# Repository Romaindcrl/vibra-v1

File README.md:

# Vibra V1

Détecteur de vibrations **XIAO ESP32S3 + LIS3DH**. Carte de **48 × 38 mm**, 2 couches, prévue pour être soudée à la main. **Révision E-HS.**

## Les fichiers utiles

| Pour… | Fichier |
|---|---|
| Ouvrir ou modifier le projet | [kicad/Vibra_V1.kicad_pro](kicad/Vibra_V1.kicad_pro) — KiCad 10.0.6 ou ultérieur |
| Lire le circuit | [Schéma PDF](rendu/schema.pdf) |
| Souder et vérifier l'implantation | [Plan de montage](rendu/montage.pdf) — page 1 agrandie, page 2 à taille réelle |
| Préparer les composants | [Liste des composants](rendu/composants.csv) |
| Faire fabriquer le PCB | [Gerbers et perçages](rendu/fabrication.zip) |

Télécharger **Code → Download ZIP**, extraire le dossier, puis ouvrir le projet. Garder le dossier `kicad/` entier : les empreintes sont intégrées au PCB, et les symboles et modèles 3D sont fournis. Toutes les instructions de montage sont ci-dessous.

**Avant fabrication : confirmer que le LIS3DH acheté est l'ancien Adafruit 2809 à une seule rangée de 8 broches. La version STEMMA QT est incompatible.** L'essai mécanique à blanc et la validation du premier prototype restent à faire. Aucun firmware de détection validé n'est fourni.

L'USB-C du XIAO alimente et programme la carte. La porteuse utilise le **3,3 V** ; le **5 V reste dans le XIAO**. Pistes de puissance et liaisons thermiques GND : **0,6 mm**. Cinq LED rouges, bouton CAL, UART sans alimentation, composants 0805 à grandes pastilles.

## Montage et mise en service

<details>
<summary><strong>Ouvrir le guide de montage</strong></summary>

### Avant de faire fabriquer

1. Vérifier le module LIS3DH : **ancien Adafruit 2809, carte carrée 20,32 mm, une seule rangée de 8 broches** dans cet ordre : VIN, 3Vo, GND, SCL, SDA, SDO, CS, INT. Le modèle STEMMA QT récent n'est pas compatible, même s'il porte aussi la référence commerciale 2809. Le capteur LIS3DH est déjà soudé sur ce module.
2. Vérifier que le XIAO est bien un ESP32S3 standard, avec deux rangées de 7 broches. Imprimer la **page 2 de [montage.pdf](rendu/montage.pdf)** à **100 %, taille réelle, sans ajustement**. Mesurer le contour : 48 × 38 mm. Faire un essai à blanc avec les modules, les barrettes et le câble USB. La page 1 agrandie ×4 est réservée à la lecture, pas à cet essai.
3. Prévoir les fixations du breakout. Il doit être rigidement lié à Vibra pour mesurer ses vibrations. H5/H6 sont deux trous de 2,5 mm, entraxe 15,24 mm. Employer de la visserie M2 et deux entretoises isolantes, diamètre extérieur ≤4 mm. Hauteur cible sous le breakout : **11,04 mm au-dessus de Vibra**, pour les barrettes choisies. Une entretoise de 11 mm peut convenir après contrôle et ajustement par rondelles fines ; ne pas plier le module en serrant. Pour deux entretoises tubulaires, prévoir deux vis M2 d'environ 16 mm, deux écrous et des rondelles isolantes ; vérifier la longueur réelle et l'absence de contact avec les composants. Ces éléments génériques figurent ici, pas sous un MPN arbitraire dans la BOM électronique.

### Pièces

La [liste unique des composants](rendu/composants.csv) donne les quantités, références fabricant et repères du plan. Les barrettes mâles ne sont nécessaires que si les modules n'en ont pas déjà. TP et H désignent des pastilles de test et des trous du PCB, sans composant à acheter.

Ajouter : le PCB, un câble USB-C **de données**, l'antenne fournie avec le XIAO branchée sur son U.FL, les fixations M2 ci-dessus et, pour fixer Vibra au support mesuré, quatre fixations M3 adaptées à ce support. Pas de batterie prévue par ce dossier. Pas de port USB-C, AZ1117, PTC ni antenne à souder sur Vibra.

### Alimentation et largeur des pistes

L'USB apporte le 5 V **au XIAO**. Son régulateur fournit le 3,3 V à Vibra par U1.12. U1.14 (5V/VBUS) reste volontairement non connecté : **aucune piste 5 V ne circule sur la carte porteuse**. Ne pas relier cette broche au 3,3 V. Ne pas alimenter la carte par J2 ou un point de test.

Toutes les pistes de puissance présentes, 3V3 et GND, sont à **0,60 mm**. La masse utilise aussi des plans sur les deux faces, avec liaisons thermiques de **0,60 mm** aux pastilles et largeur minimale de cuivre de **0,60 mm**. Une règle KiCad impose cette largeur minimale aux pistes GND/3V3 et réserve la même limite aux éventuels réseaux 5V/VBUS. Les traits verts du schéma représentent des connexions logiques ; leur épaisseur sur papier n'est pas la largeur du cuivre.

Si le professeur exige une piste 5 V physiquement présente sur la porteuse, cela constitue une autre architecture à valider : la présente version respecte le choix d'alimenter uniquement par le XIAO.

### Ordre de soudure

La **page 1 de [montage.pdf](rendu/montage.pdf)** indique tous les repères, avec l'USB vers le haut. Tout se pose sur la face supérieure ; les barrettes traversantes se soudent au dos. Ne jamais souder avec l'USB branché.

1. Trier les résistances et condensateurs, puis souder R4/R7/R8/R9–R13 et C5/C6/C8/C9/C10. Ils ne sont pas polarisés. Déposer un peu d'étain sur une pastille, positionner la pièce à la pince, la fixer puis souder l'autre côté avec du flux. Les pastilles 0805 dépassent du corps pour laisser passer la panne.
2. Souder D1–D5. **Cathode K = pastille 1 = GND, à gauche sur ce plan ; anode A = pastille 2, à droite.** Vérifier la polarité du composant au mode diode avant de le poser ; ne pas se fier uniquement à sa couleur. Les cinq LED ont le même sens.
3. Souder SW2/CAL : aligner les quatre pattes avec les quatre pastilles. Le composant relie déjà 1 à 2 et 3 à 4 en interne ; l'appui relie les deux paires. Ne pas le tourner de 90°. L'orientation à 180° conserve la fonction.
4. Souder J2 et les supports femelles U1/J3. Immobiliser les barrettes perpendiculaires à la carte ; souder d'abord une broche, vérifier l'alignement, puis les autres. Garder les modules débranchés pendant la chauffe ; un gabarit mécanique hors tension peut servir à aligner les deux supports U1.
5. Si nécessaire, souder les mâles sous les modules, extrémités courtes dans les cartes et longues vers les supports. Vérifier les joints, les ponts d'étain et nettoyer les résidus selon le flux utilisé.
6. Effectuer les contrôles hors tension ci-dessous. Enficher ensuite le XIAO, **USB vers l'extérieur du bord supérieur**. Enficher le LIS3DH composants vers le haut, **VIN dans J3.1, carré, côté bas marqué 1 VIN**. Aucune broche ne doit dépasser latéralement du support. Les 0805 sous le breakout doivent avoir été soudés avant cette étape.
7. Fixer le breakout à H5/H6 sans fléchir son PCB. Fixer Vibra au support à mesurer par ses quatre trous M3. Prévoir l'emplacement de l'antenne XIAO dans le boîtier, à l'écart du métal ; elle et les entretoises ne sont pas représentées en 3D.

La masse à 0,6 mm absorbe davantage de chaleur qu'une piste signal : chauffer ensemble la patte et la pastille, utiliser du flux et une panne adaptée. Les liaisons thermiques sont conservées pour faciliter cette opération ; ne pas compenser un mauvais contact par une chauffe prolongée du composant.

### Contrôles avant le premier branchement

Modules retirés et USB débranché : vérifier l'absence de pont entre 3V3 (TP3) et GND (TP4). Un bref bip dû à la charge des condensateurs n'est pas à lui seul un court-circuit ; une résistance très faible persistante exige de rechercher le défaut. Ne pas mesurer la résistance sur une carte alimentée.

Vérifier au multimètre : TP4 ↔ U1.13/J2.1/J3.3/J3.6 ; TP3 ↔ U1.12/J3.1/J3.7 ; CAL TP6 ↔ U1.3. CAL devient conducteur vers GND à l'appui. U1.14 et J3.2 doivent rester sans liaison aux autres réseaux. Vérifier l'orientation des LED au mode diode ; la méthode peut être perturbée par les chemins en parallèle après montage.

### Première mise sous tension et logiciel

Brancher seulement l'USB du XIAO, avec les modules en place. Mesurer environ **3,3 V entre TP3 et TP4**. Si une pièce chauffe anormalement ou si la tension s'effondre, débrancher et inspecter le montage. Vérifier ensuite le 3,3 V au démarrage et lors des émissions Wi-Fi.

Le dossier est une conception matérielle : **aucun firmware de détection/calibration validé n'est fourni**. Pour la mise au point du logiciel :

| Fonction | Test attendu |
|---|---|
| USB | XIAO détecté et programmable ; utiliser ses boutons BOOT/RESET si nécessaire |
| I²C | SDA GPIO5, SCL GPIO6 ; commencer à 100 kHz ; LIS3DH détecté à 0x18 |
| Identité capteur | WHO_AM_I, registre 0x0F, retourne 0x33 |
| Interruption | INT1 relié à GPIO9 ; configurer l'interruption dans le LIS3DH avant le test |
| LED | GPIO1, 2, 4, 7, 8 ; état haut = allumée ; 680 Ω chacune, courant de l'ordre de 2 mA |
| CAL | GPIO3 ; haut au repos, bas à l'appui ; prévoir l'anti-rebond logiciel |
| UART facultatif | J2.1 GND, J2.2 TX(GPIO43), J2.3 RX(GPIO44) ; logique 3,3 V, TX/RX croisés, sans VCC |

CAL ne remplace pas BOOT. Le GPIO3 a aussi une fonction de sélection JTAG au démarrage selon les eFuses ; laisser CAL relâché lors du démarrage et voir le brochage ci-dessous. Le comportement réel du détecteur et sa calibration devront être vérifiés avec le firmware sur un prototype rigidement fixé.

### Fichiers de fabrication

Ouvrir [`kicad/Vibra_V1.kicad_pro`](kicad/Vibra_V1.kicad_pro) dans KiCad 10.0.6 ou ultérieur. Fabrication : FR-4 **1,6 mm**, **2 couches**, cuivre nominal **35 µm**, masque sur les deux faces. Les Gerbers et perçages sont réunis dans **[fabrication.zip](rendu/fabrication.zip)** ; ne pas mélanger les révisions.

Il s'agit d'un PCB à faire fabriquer puis à assembler à domicile. Les vias et trous métallisés requis ne sont pas adaptés à une simple gravure maison sans métallisation.

La vérification numérique est propre, mais elle ne remplace pas la confirmation du breakout acheté, l'essai mécanique à blanc et les mesures sur le premier exemplaire. Aucune commande n'a été passée.

</details>

<details>
<summary><strong>Brochage complet</strong></summary>

Vue de dessus, USB du XIAO vers le bord supérieur. Deux rangées de 7 broches au pas de 2,54 mm, espacées de 15,24 mm. Pastille carrée 1 = D0, en haut à gauche. Une seule alimentation : USB-C du XIAO. Sa broche 5V/VBUS reste isolée de la carte porteuse.

| U1 | Marquage XIAO | GPIO S3 | Fonction Vibra |
|---:|---|---:|---|
| 1 | D0 | 1 | LED1 |
| 2 | D1 | 2 | LED2 |
| 3 | D2 | 3 | CAL, actif à zéro, pull-up 10 kΩ |
| 4 | D3 | 4 | LED3 |
| 5 | D4 / SDA | 5 | I²C SDA |
| 6 | D5 / SCL | 6 | I²C SCL |
| 7 | D6 / TX | 43 | UART TX → J2.2 |
| 8 | D7 / RX | 44 | UART RX ← J2.3 |
| 9 | D8 | 7 | LED4 |
| 10 | D9 | 8 | LED5 |
| 11 | D10 | 9 | LIS3DH INT1 |
| 12 | 3V3 | — | Sortie régulée du XIAO vers Vibra |
| 13 | GND | — | Masse commune |
| 14 | 5V | — | Non connectée |

Les LED sont actives à l'état haut, chacune avec 680 Ω. Les numéros GPIO de l'ancien ESP32-C3 ne sont plus valables. Initialiser I²C sur SDA=5, SCL=6 et INT1 sur GPIO9. Ne pas confondre D10 (GPIO9) et GPIO10. CAL ne met pas le XIAO en mode téléchargement ; employer ses boutons BOOT et RESET pour cette fonction.

GPIO3 est aussi une broche de sélection JTAG au reset selon les eFuses. CAL peut donc affecter cette sélection si ces eFuses ont été configurés ; il ne remplace pas GPIO0/BOOT. Référence : [Espressif](https://documentation.espressif.com/esp32-s3_datasheet_en.pdf).

| J3 | Ancien breakout Adafruit 2809 | Connexion |
|---:|---|---|
| 1, carré, côté bas | VIN | +3V3 du XIAO |
| 2 | 3Vo | Non connectée |
| 3 | GND | GND |
| 4 | SCL | GPIO6 |
| 5 | SDA | GPIO5 |
| 6 | SDO | GND : adresse 0x18 |
| 7 | CS | +3V3 : mode I²C |
| 8, côté haut | INT | GPIO9 |

J2 : 1 GND, 2 TX, 3 RX. Relier TX de l'adaptateur au RX de Vibra et inversement. Adaptateur logique 3,3 V ; ne raccorder aucune sortie d'alimentation de l'adaptateur.

</details>

<details>
<summary><strong>Contrôles KiCad et modification du projet</strong></summary>

Contrôles dans KiCad 10.0.6 : **DRC : 0 erreur, 0 avertissement, 0 liaison non routée et 0 écart schéma/PCB. ERC : 0 erreur et 34 avertissements de liaison aux empreintes.** Ces avertissements viennent de la suppression de la bibliothèque d'empreintes séparée ; le contrôle reste actif. La revue de Rev E a aussi confirmé **71/71 associations broche–réseau**. Les fichiers détaillés de la revue restent accessibles dans l'historique Git ; le dossier de rendu ne contient que les fichiers utiles à la réalisation.

Les 34 empreintes complètes, dont les grandes pastilles de soudure manuelle, restent intégrées au fichier `.kicad_pcb`. Pour réutiliser une empreinte personnalisée sur un nouveau composant, l'exporter depuis le PCB vers une bibliothèque personnelle, puis l'assigner dans le schéma. La bibliothèque d'origine reste récupérable dans l'historique Git.

Cinq contrôles DRC hérités restent désactivés : centrage piste/via, géométrie des profils de tuning, filtres d'empreintes, PTH dans courtyard, NPTH dans courtyard. Quatre ERC restent désactivés : filtres d'empreintes, jonctions à quatre branches, modèle SPICE, label global unique. Aucune exclusion individuelle DRC. Les contrôles électriques, d'isolation, thermiques, de perçage, de routage et de parité sont actifs.

Après une modification : mettre le PCB à jour depuis le schéma, remplir et sauvegarder les zones, relancer ERC et DRC avec parité, puis régénérer les fichiers de fabrication. Les contrôles numériques ne remplacent pas les essais physiques.

</details>

<details>
<summary><strong>Sources et attributions</strong></summary>

- Seeed : https://wiki.seeedstudio.com/xiao_esp32s3_getting_started/
- SKU du XIAO ESP32S3 : https://www.seeedstudio.com/XIAO-ESP32S3-p-5627.html
- Empreinte porteuse dérivée des positions DIP officielles, sans pastilles CMS : https://files.seeedstudio.com/wiki/XIAO-KiCad-Library/New_XIAO_Series_Footprints.zip
- Symboles officiels, utilisés pour vérifier le brochage à 14 broches : https://files.seeedstudio.com/wiki/XIAO-KiCad-Library/XIAO_Series_SCH_Symbols.zip
- Modèle STEP officiel : https://files.seeedstudio.com/wiki/SeeedStudio-XIAO-ESP32S3/res/seeed-studio-xiao-esp32s3-3d_model.zip
- Embases XIAO : https://www.we-online.com/components/products/datasheet/61300711821.pdf (7 broches, pas 2,54, entre première et dernière 15,24, hauteur 8,5, perçage recommandé 1,02 ±0,15)
- Broches mâles XIAO : https://www.we-online.com/components/products/datasheet/61300711121.pdf
- GPIO3 et JTAG : https://documentation.espressif.com/esp32-s3_datasheet_en.pdf
- Adafruit original et STEMMA QT : https://github.com/adafruit/Adafruit-LIS3DH-Breakout-PCB

Les modèles génériques des barrettes proviennent des bibliothèques KiCad installées ; leurs enveloppes sont indicatives. Les modèles et fichiers Seeed conservent leur provenance ; aucune revendication de création originale. Les fichiers téléchargés sont des données CAO, pas des instructions d'exécution.

- Registre WHO_AM_I 0x33 : https://raw.githubusercontent.com/adafruit/Adafruit_LIS3DH/master/Adafruit_LIS3DH.cpp

- Géométrie exacte du breakout ancien : `Adafruit LIS3DH Breakout Original.brd`, dépôt officiel Adafruit ci-dessus. Contour 20,32 × 20,32 mm, trous 2,5 mm à (2,54 ; 17,78) et (17,78 ; 17,78). Source disponible dans le dépôt officiel Adafruit lié ci-dessus.
- Modèle 3D bleu : adaptation simplifiée créée pour cette révision à partir du PCB Adafruit. Contour, perçages et centres des composants issus du fichier Eagle ; volumes des composants approximatifs. Ce n'est pas un modèle STEP officiel Adafruit. Attribution ci-dessous ; licence jointe dans `kicad/licenses/`.

## Vérification Rev E-HS — 27 septembre 2026

- C&K PTS526, fiche fabricant du 4 avril 2022, page 2 : contacts 1–2 et 3–4 reliés en interne ; fermeture entre les deux paires à l'appui. Implantation G-leads sans broche de masse, hauteur 1,5 mm. Pastilles fabricant 1,0 × 0,7 mm, entraxes 6,0 × 3,7 mm ; adaptation manuelle 1,2 × 0,8 mm étendue vers l'extérieur, intervalle intérieur 5,0 mm conservé. [Fiche C&K](https://www.ckswitches.com/media/2780/pts526.pdf), [copie fabricant consultée](https://4donline.ihs.com/images/VipMasterIC/IC/CKCI/CKCI-S-A0014471833/CKCI-S-A0014948334-1.pdf?hkey=6D3A4C79FDBF58556ACFDE234799DDF0).
- Documentation Seeed relue : brochage XIAO ESP32S3, sortie 3V3, USB-C et antenne U.FL. L'antenne fournie avec le XIAO n'est pas une antenne ajoutée à la carte porteuse.
- LED : symbole graphique standard KiCad `Device:LED`, adapté aux positions des broches existantes. Bibliothèques KiCad : https://www.kicad.org/libraries/license/ (CC-BY-SA 4.0 avec exception KiCad pour les conceptions).

Les contrôles de prix, de stock et de révision de la pièce effectivement achetée ne font pas partie des validations numériques.

### Modèle Adafruit

PCB original conçu par Limor Fried/Ladyada pour Adafruit Industries :
https://github.com/adafruit/Adafruit-LIS3DH-Breakout-PCB

Le modèle `Adafruit_LIS3DH_2809_Original.step` est une adaptation réalisée pour Vibra Rev D le 25 septembre 2026. Il reprend le contour, les perçages et les positions de composants du PCB original ; les volumes des composants et couleurs sont simplifiés. Il n'inclut pas la sérigraphie officielle. Il est distribué sous la même licence Creative Commons Attribution-ShareAlike 3.0, jointe ici. Adafruit n'a pas validé cette adaptation.

Le fichier Eagle original et ses révisions sont disponibles dans le dépôt officiel Adafruit lié ci-dessus. Les autres modèles conservent leurs provenances Seeed et KiCad détaillées ici.

[Licence CC BY-SA 3.0 du modèle Adafruit](kicad/licenses/Adafruit_CC_BY_SA_3.0.txt). Les éléments tiers conservent leurs licences respectives. Aucune licence globale supplémentaire n'est accordée par ce dépôt.

</details>

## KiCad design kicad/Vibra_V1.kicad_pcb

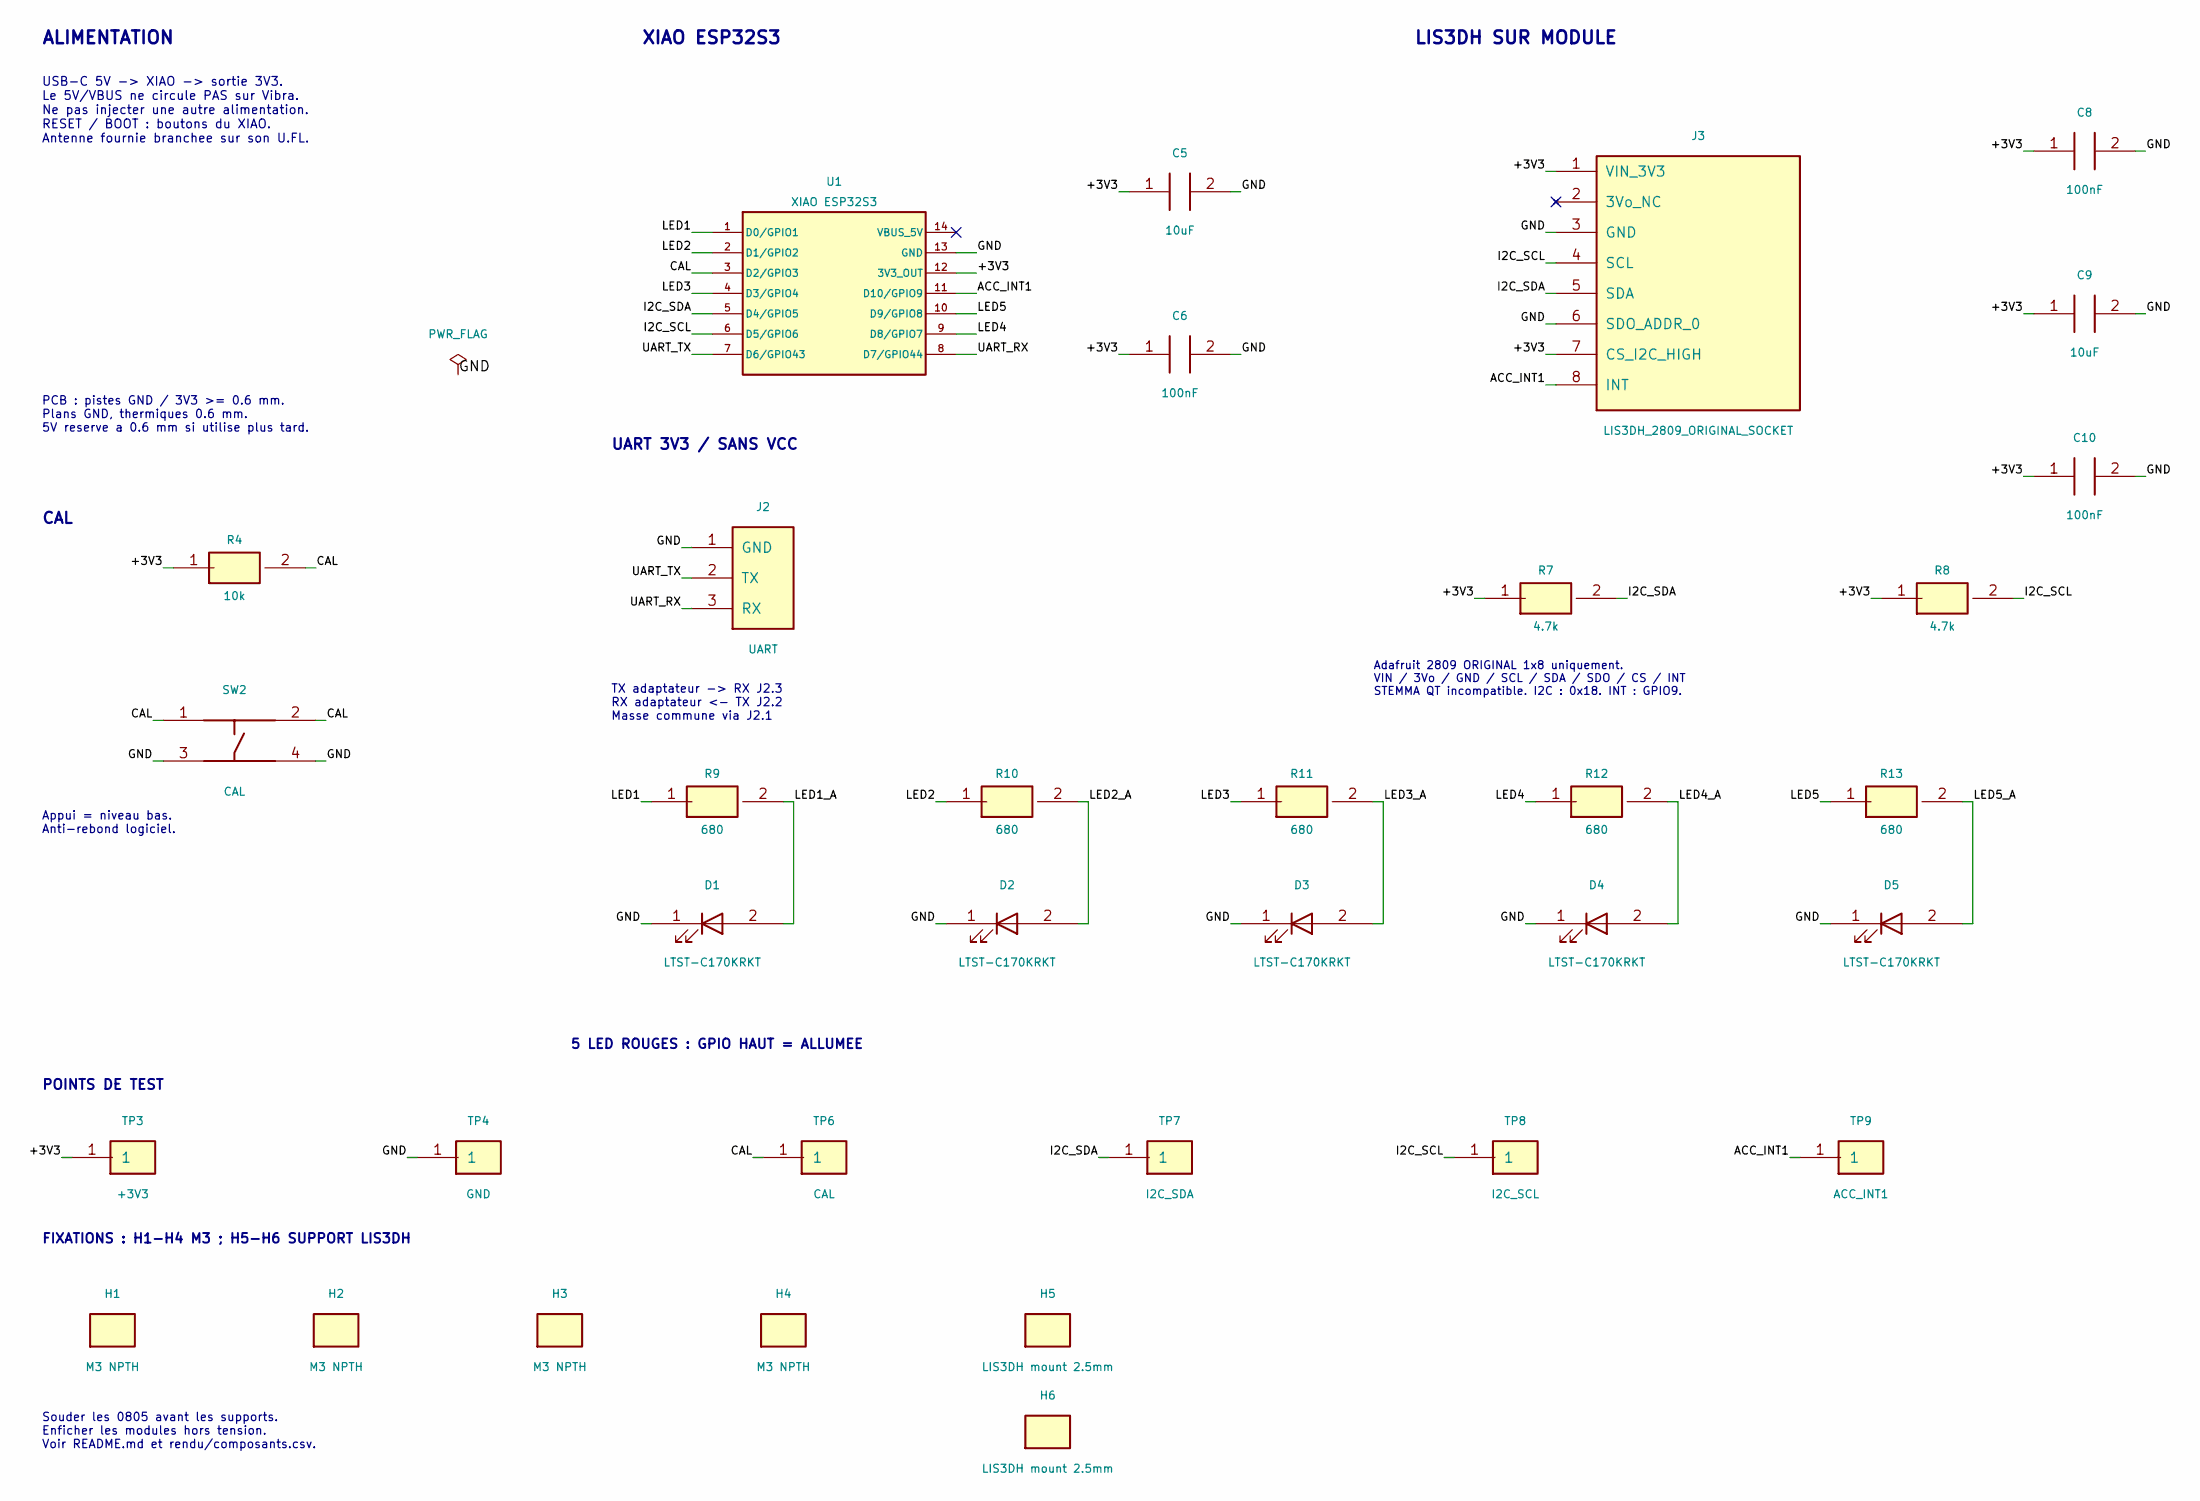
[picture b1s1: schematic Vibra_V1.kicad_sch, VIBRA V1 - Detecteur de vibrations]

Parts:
C5, C9: 10uF; C_0805_2012Metric_Pad1.18x1.45mm_HandSolder; MPN GRM21BR61C106KE15L
C6, C8, C10: 100nF; C_0805_2012Metric_Pad1.18x1.45mm_HandSolder; MPN GRM21BR71C104KA01L
D1, D2, D3, D4, D5: LTST-C170KRKT; LED_0805_2012Metric_Pad1.15x1.40mm_HandSolder; MPN LTST-C170KRKT
H1, H2, H3, H4: M3 NPTH; MountingHole_3.2mm_M3; MPN N/A
H5, H6: LIS3DH mount 2.5mm; MountingHole_2.5mm; MPN N/A
J2: UART; UART_1x03_2.54mm_Drill1.10; MPN 61300311121
J3: LIS3DH_2809_ORIGINAL_SOCKET; Socket_1x08_2.54mm_H8.5; MPN 61300811821
R4: 10k; R_0805_2012Metric_Pad1.20x1.40mm_HandSolder; MPN RC0805FR-0710KL
R7, R8: 4.7k; R_0805_2012Metric_Pad1.20x1.40mm_HandSolder; MPN RC0805FR-074K7L
R9, R10, R11, R12, R13: 680; R_0805_2012Metric_Pad1.20x1.40mm_HandSolder; MPN RC0805FR-07680RL
SW2: CAL; PTS526SK15SMTR2LFS; MPN PTS526 SK15 SMTR2 LFS
TP3: +3V3; TestPoint_Pad_D1.5mm; MPN N/A
TP4: GND; TestPoint_Pad_D1.5mm; MPN N/A
TP6: CAL; TestPoint_Pad_D1.5mm; MPN N/A
TP7: I2C_SDA; TestPoint_Pad_D1.5mm; MPN N/A
TP8: I2C_SCL; TestPoint_Pad_D1.5mm; MPN N/A
TP9: ACC_INT1; TestPoint_Pad_D1.5mm; MPN N/A
U1: XIAO ESP32S3; XIAO_ESP32S3_Sockets; MPN 113991114

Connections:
/+3V3: C5.1, C6.1, C8.1, C9.1, C10.1, J3.1 (VIN_3V3), J3.7 (CS_I2C_HIGH), R4.1, R7.1, R8.1, TP3.1, U1.12 (3V3_OUT)
/ACC_INT1: J3.8 (INT), TP9.1, U1.11 (D10/GPIO9)
/CAL: R4.2, SW2.1 (A1), SW2.2 (A2), TP6.1, U1.3 (D2/GPIO3)
/GND: C5.2, C6.2, C8.2, C9.2, C10.2, D1.1 (K), D2.1 (K), D3.1 (K), D4.1 (K), D5.1 (K), J2.1 (GND), J3.3 (GND), J3.6 (SDO_ADDR_0), SW2.3 (B1), SW2.4 (B2), TP4.1, U1.13 (GND)
/I2C_SCL: J3.4 (SCL), R8.2, TP8.1, U1.6 (D5/GPIO6)
/I2C_SDA: J3.5 (SDA), R7.2, TP7.1, U1.5 (D4/GPIO5)
/LED1: R9.1, U1.1 (D0/GPIO1)
/LED1_A: D1.2 (A), R9.2
/LED2: R10.1, U1.2 (D1/GPIO2)
/LED2_A: D2.2 (A), R10.2
/LED3: R11.1, U1.4 (D3/GPIO4)
/LED3_A: D3.2 (A), R11.2
/LED4: R12.1, U1.9 (D8/GPIO7)
/LED4_A: D4.2 (A), R12.2
/LED5: R13.1, U1.10 (D9/GPIO8)
/LED5_A: D5.2 (A), R13.2
/UART_RX: J2.3 (RX), U1.8 (D7/GPIO44)
/UART_TX: J2.2 (TX), U1.7 (D6/GPIO43)

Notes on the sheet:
ALIMENTATION
UART 3V3 / SANS VCC
XIAO ESP32S3
Adafruit 2809 ORIGINAL 1x8 uniquement. VIN / 3Vo / GND / SCL / SDA / SDO / CS / INT STEMMA QT incompatible. I2C : 0x18. INT : GPIO9.
Appui = niveau bas. Anti-rebond logiciel.
PCB : pistes GND / 3V3 >= 0.6 mm. Plans GND, thermiques 0.6 mm. 5V reserve a 0.6 mm si utilise plus tard.
LIS3DH SUR MODULE
USB-C 5V -> XIAO -> sortie 3V3. Le 5V/VBUS ne circule PAS sur Vibra. Ne pas injecter une autre alimentation. RESET / BOOT : boutons du XIAO. Antenne fournie branchee sur son U.FL.
5 LED ROUGES : GPIO HAUT = ALLUMEE
Souder les 0805 avant les supports. Enficher les modules hors tension. Voir README.md et rendu/composants.csv.
FIXATIONS : H1-H4 M3 ; H5-H6 SUPPORT LIS3DH
TX adaptateur -> RX J2.3 RX adaptateur <- TX J2.2 Masse commune via J2.1
POINTS DE TEST
CAL

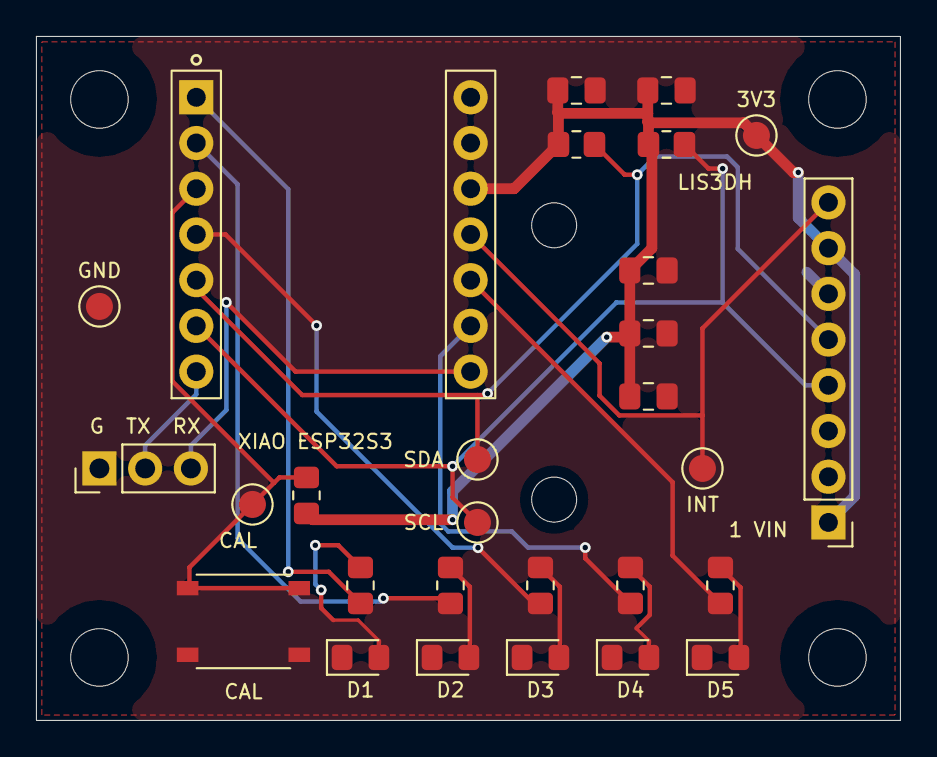
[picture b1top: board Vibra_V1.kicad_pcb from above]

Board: 2 copper layers, 48.0 x 38.0 mm, 34 parts (0 on the bottom side), 18 nets.

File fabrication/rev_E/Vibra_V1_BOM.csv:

Reference,Qty,Value,Footprint,MPN,Description,Assembly
U1,1,XIAO ESP32S3,Vibra_Reviewed:XIAO_ESP32S3_Sockets,113991114,Seeed XIAO ESP32S3 sur 2 embases 1x7; USB-C du XIAO; 3V3 sortie,User supplied module on sockets
J3,1,LIS3DH_2809_ORIGINAL_SOCKET,Vibra_Reviewed:Socket_1x08_2.54mm_H8.5,61300811821,8.5 mm high female socket for Adafruit 2809 ORIGINAL 1x8 only; not STEMMA QT,Populate
R4,1,10k,Vibra_Reviewed:R_0805_2012Metric_Pad1.20x1.40mm_HandSolder,RC0805FR-0710KL,CAL pull-up,Populate
R7,1,4.7k,Vibra_Reviewed:R_0805_2012Metric_Pad1.20x1.40mm_HandSolder,RC0805FR-074K7L,I2C SDA pull-up,Populate
R8,1,4.7k,Vibra_Reviewed:R_0805_2012Metric_Pad1.20x1.40mm_HandSolder,RC0805FR-074K7L,I2C SCL pull-up,Populate
R9,1,680,Vibra_Reviewed:R_0805_2012Metric_Pad1.20x1.40mm_HandSolder,RC0805FR-07680RL,LED1 current limit,Populate
D1,1,LTST-C170KRKT,Vibra_Reviewed:LED_0805_2012Metric_Pad1.15x1.40mm_HandSolder,LTST-C170KRKT,Red vibration level LED 1,Populate
R10,1,680,Vibra_Reviewed:R_0805_2012Metric_Pad1.20x1.40mm_HandSolder,RC0805FR-07680RL,LED2 current limit,Populate
D2,1,LTST-C170KRKT,Vibra_Reviewed:LED_0805_2012Metric_Pad1.15x1.40mm_HandSolder,LTST-C170KRKT,Red vibration level LED 2,Populate
R11,1,680,Vibra_Reviewed:R_0805_2012Metric_Pad1.20x1.40mm_HandSolder,RC0805FR-07680RL,LED3 current limit,Populate
D3,1,LTST-C170KRKT,Vibra_Reviewed:LED_0805_2012Metric_Pad1.15x1.40mm_HandSolder,LTST-C170KRKT,Red vibration level LED 3,Populate
R12,1,680,Vibra_Reviewed:R_0805_2012Metric_Pad1.20x1.40mm_HandSolder,RC0805FR-07680RL,LED4 current limit,Populate
D4,1,LTST-C170KRKT,Vibra_Reviewed:LED_0805_2012Metric_Pad1.15x1.40mm_HandSolder,LTST-C170KRKT,Red vibration level LED 4,Populate
R13,1,680,Vibra_Reviewed:R_0805_2012Metric_Pad1.20x1.40mm_HandSolder,RC0805FR-07680RL,LED5 current limit,Populate
D5,1,LTST-C170KRKT,Vibra_Reviewed:LED_0805_2012Metric_Pad1.15x1.40mm_HandSolder,LTST-C170KRKT,Red vibration level LED 5,Populate
C5,1,10uF,Vibra_Reviewed:C_0805_2012Metric_Pad1.18x1.45mm_HandSolder,GRM21BR61C106KE15L,ESP32 local bulk,Populate
C6,1,100nF,Vibra_Reviewed:C_0805_2012Metric_Pad1.18x1.45mm_HandSolder,GRM21BR71C104KA01L,ESP32 bypass,Populate
C8,1,100nF,Vibra_Reviewed:C_0805_2012Metric_Pad1.18x1.45mm_HandSolder,GRM21BR71C104KA01L,LIS3DH breakout connector bypass,Populate
C9,1,10uF,Vibra_Reviewed:C_0805_2012Metric_Pad1.18x1.45mm_HandSolder,GRM21BR61C106KE15L,LIS3DH breakout local bulk,Populate
C10,1,100nF,Vibra_Reviewed:C_0805_2012Metric_Pad1.18x1.45mm_HandSolder,GRM21BR71C104KA01L,LIS3DH breakout auxiliary bypass,Populate
SW2,1,CAL,Vibra_Reviewed:PTS526SK15SMTR2LFS,PTS526 SK15 SMTR2 LFS,PTS526 SK15: pads extended to 1.2 x 0.8 mm for hand soldering; same pin numbering as professor part,Populate
J2,1,UART,Vibra_Reviewed:UART_1x03_2.54mm_Drill1.10,61300311121,"3-pin UART header, no power pin",Populate
TP3,1,+3V3,Vibra_Reviewed:TestPoint_Pad_D1.5mm,N/A,Exposed copper test point: +3V3,PCB feature
TP4,1,GND,Vibra_Reviewed:TestPoint_Pad_D1.5mm,N/A,Exposed copper test point: GND,PCB feature
TP6,1,CAL,Vibra_Reviewed:TestPoint_Pad_D1.5mm,N/A,Exposed copper test point: CAL,PCB feature
TP7,1,I2C_SDA,Vibra_Reviewed:TestPoint_Pad_D1.5mm,N/A,Exposed copper test point: I2C_SDA,PCB feature
TP8,1,I2C_SCL,Vibra_Reviewed:TestPoint_Pad_D1.5mm,N/A,Exposed copper test point: I2C_SCL,PCB feature
TP9,1,ACC_INT1,Vibra_Reviewed:TestPoint_Pad_D1.5mm,N/A,Exposed copper test point: ACC_INT1,PCB feature
H1,1,M3 NPTH,Vibra_Reviewed:MountingHole_3.2mm_M3,N/A,3.2 mm non-plated mounting hole,PCB feature
H2,1,M3 NPTH,Vibra_Reviewed:MountingHole_3.2mm_M3,N/A,3.2 mm non-plated mounting hole,PCB feature
H3,1,M3 NPTH,Vibra_Reviewed:MountingHole_3.2mm_M3,N/A,3.2 mm non-plated mounting hole,PCB feature
H4,1,M3 NPTH,Vibra_Reviewed:MountingHole_3.2mm_M3,N/A,3.2 mm non-plated mounting hole,PCB feature
U1 sockets,2,Female 1x7 2.54mm H8.5,Included in U1 combined footprint,61300711821,"Solder these two socket strips to Vibra, not the XIAO itself",Populate
U1 male headers,2,Male 1x7 2.54mm,On XIAO underside,61300711121,Short ends soldered through XIAO; long ends point down into sockets,If not already fitted
J3 breakout,1,Adafruit LIS3DH 2809 ORIGINAL 1x8,Plug into J3; match pin legend,2809 (original 1x8 revision only),"VIN,3Vo,GND,SCL,SDA,SDO,CS,INT; modern STEMMA QT is incompatible; board 20.32 x 20.32 mm; secure through H5/H6",Hardware revision must be confirmed
J3 male header,1,Male 1x8 2.54mm,On breakout underside,61300811121,Populate only if missing on the purchased original breakout,If not already fitted
H5,1,LIS3DH mount 2.5mm,Vibra_Reviewed:MountingHole_2.5mm,N/A,2.5 mm NPTH aligned to original Adafruit breakout mounting hole,PCB feature
H6,1,LIS3DH mount 2.5mm,Vibra_Reviewed:MountingHole_2.5mm,N/A,2.5 mm NPTH aligned to original Adafruit breakout mounting hole,PCB feature
